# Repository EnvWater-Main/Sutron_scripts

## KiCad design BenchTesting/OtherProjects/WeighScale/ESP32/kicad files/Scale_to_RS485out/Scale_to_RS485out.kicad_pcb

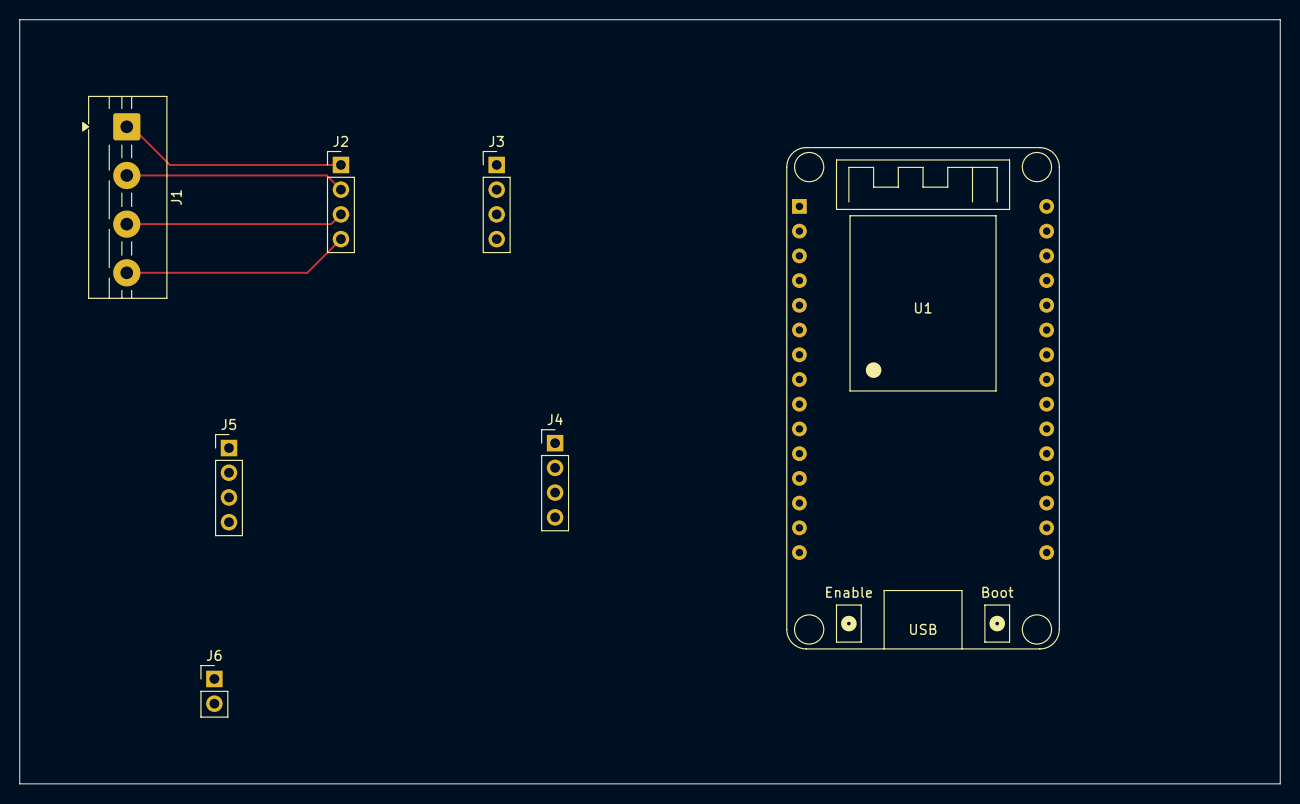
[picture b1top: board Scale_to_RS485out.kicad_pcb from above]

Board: 2 copper layers, 129.5 x 78.5 mm, 7 parts (0 on the bottom side), 9 nets.

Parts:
J1: Screw_Terminal_01x04; TerminalBlock_MaiXu_MX126-5.0-04P_1x04_P5.00mm
J2, J3, J4, J5: Conn_01x04_Socket; PinHeader_1x04_P2.54mm_Vertical
J6: Conn_01x02_Socket; PinHeader_1x02_P2.54mm_Vertical
U1: ESP32_DevKit_V1_DOIT; esp32_devkit_v1_doit

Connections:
A+: J1.4, J2.4
A-: J1.3, J2.3
DE: U1.25 (IO19), U1.26 (IO21)
DT: J3.3, U1.7 (IO33)
E+: J1.1, J2.1
E-: J1.2, J2.2
GND: J3.4, J5.4, U1.14 (GND), U1.17 (GND)
SCK: J3.2, U1.8 (IO25), U1.30 (IO23)
VCC: J3.1, J5.1, U1.15 (VIN)

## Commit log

2026-02-12 reorganizing
2026-02-12 reorganizing again
2026-02-12 add arduino
2026-02-12 updated generic script
2026-02-12 updated generic
